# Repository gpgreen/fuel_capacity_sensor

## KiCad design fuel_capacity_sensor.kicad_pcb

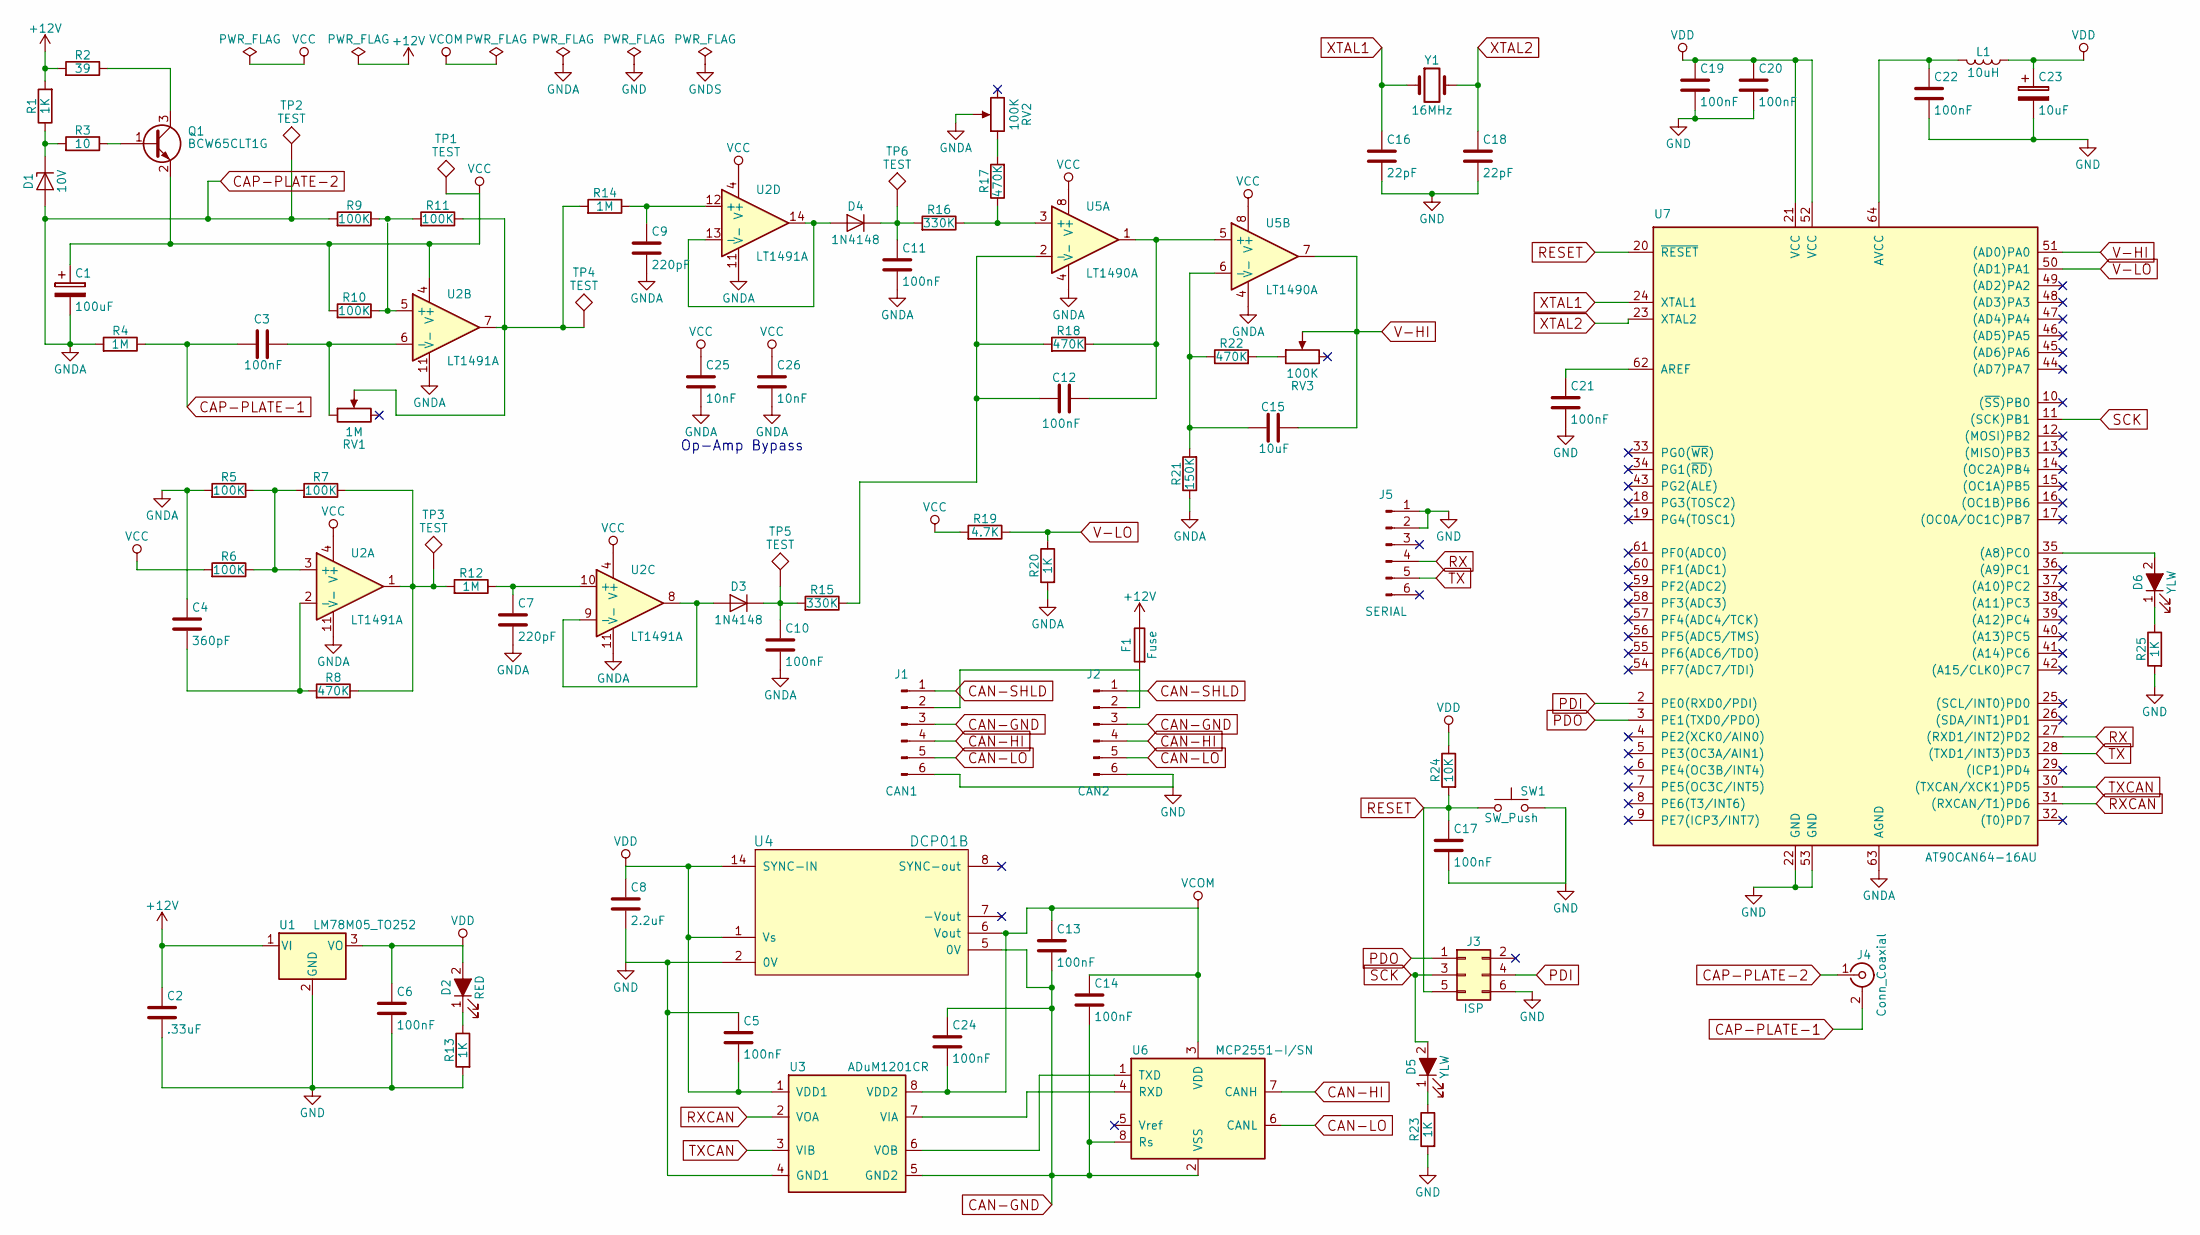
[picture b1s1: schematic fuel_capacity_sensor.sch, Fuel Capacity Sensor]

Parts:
C1: 100uF; C_0603
C2: .33uF; C_0603
C3, C5, C6, C10, C11, C12, C13, C14, C17, C19, C20, C21, C22, C24: 100nF; C_0603
C4: 360pF; C_0603
C7, C9: 220pF; C_0603
C8: 2.2uF; C_0603
C15: 10uF; C_0603
C16, C18: 22pF; C_0603
C23: 10uF; CP_Tantalum_Case-A_EIA-3216-18_Reflow
C25, C26: 10nF; C_0603
D1: 10V; D_SOD-123F
D2: RED; D_SOD-123F
D3, D4: 1N4148; D_SOD-123F
D5, D6: YLW; D_SOD-123F
F1: Fuse; Fuse_SMD1206_Reflow
J1: CAN1; JST_XH_B06B-XH-A_06x2.50mm_Straight
J2: CAN2; JST_XH_B06B-XH-A_06x2.50mm_Straight
J3: ISP
J4: Conn_Coaxial; bnc-ci
J5: SERIAL; Pin_Header_Straight_1x06_Pitch2.54mm
L1: 10uH; L_1206
Q1: BCW65CLT1G; SOT-23
R1, R13, R20, R23, R25: 1K; R_0603
R2: 39; R_0603
R3: 10; R_0603
R4, R12, R14: 1M; R_0603
R5, R6, R7, R9, R10, R11: 100K; R_0603
R8, R17, R18, R22: 470K; R_0603
R15, R16: 330K; R_0603
R19: 4.7K; R_0603
R21: 150K; R_0603
R24: 10K; R_0603
RV1: 1M; Potentiometer_Trimmer_Copal_CT-6EP
RV2, RV3: 100K; Potentiometer_Trimmer_Copal_CT-6EP
SW1: SW_Push; switch-kpt-1187B-SMD
TP1, TP2, TP3, TP4, TP5, TP6: TEST; Test_Point_Keystone_5015_Micro-Minature
U1: LM78M05_TO252; TO-252-2
U2: LT1491A; SOIC-16_3.9x9.9mm_Pitch1.27mm
U3: ADuM1201CR; SOIC-8_3.9x4.9mm_Pitch1.27mm
U4: DCP01B; DCP01B_SO_7_14
U5: LT1490A; SOIC-8_3.9x4.9mm_Pitch1.27mm
U6: MCP2551-I/SN; SOIC-8_3.9x4.9mm_Pitch1.27mm
U7: AT90CAN64-16AU; TQFP-64_10x10mm_Pitch0.5mm
Y1: 16MHz; Crystal_SMD_HC49-SD

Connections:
+12V: C2.1, F1.1, R1.2, R2.2, U1.1 (VI)
CAN-GND: C13.2, C14.2, C24.1, J1.3, J2.3, U3.5 (GND2), U4.5 (0V), U6.2 (VSS), U6.8 (Rs)
CAN-HI: J1.4, J2.4, U6.7 (CANH)
CAN-LO: J1.5, J2.5, U6.6 (CANL)
CAN-SHLD: J1.1, J2.1
CAP-PLATE-1: C3.1, J4.2 (Ext), R4.1
CAP-PLATE-2: C1.2, C4.1, C7.2, C9.2, C10.2, C11.2, C25.2, C26.2, D1.2 (A), J4.1 (In), R4.2, R5.2, R9.2, R20.2, R21.1, RV2.2, TP2.1, U2.11 (V-), U5.4 (V-), U7.63 (AGND)
GND: C2.2, C5.1, C6.2, C8.2, C16.2, C17.2, C18.2, C19.2, C20.2, C21.2, C22.2, C23.2, J1.6, J2.6, J3.6, J5.1, J5.2, R13.2, R23.2, R25.2, SW1.2, U1.2 (GND), U3.4 (GND1), U4.2 (0V), U7.22 (GND), U7.53 (GND)
unnamed: C3.2, RV1.1, U2.6 (-)
unnamed: C4.2, R8.2, U2.2 (-)
unnamed: C7.1, R12.1, U2.10 (+)
unnamed: C9.1, R14.1, U2.12 (+)
unnamed: C10.1, D3.1 (K), R15.2, TP5.1
unnamed: C11.1, D4.1 (K), R16.2, TP6.1
unnamed: C12.1, R15.1, R18.2, U5.2 (-)
unnamed: C12.2, R18.1, U5.1, U5.5 (+)
unnamed: C15.1, R21.2, R22.1, U5.6 (-)
unnamed: C21.1, U7.62 (AREF)
unnamed: C22.1, L1.2, U7.64 (AVCC)
unnamed: D1.1 (K), R1.1, R3.2
unnamed: D2.1 (K), R13.1
unnamed: D3.2 (A), U2.8, U2.9 (-)
unnamed: D4.2 (A), U2.13 (-), U2.14
unnamed: D5.1 (K), R23.1
unnamed: D6.1 (K), R25.1
unnamed: D6.2 (A), U7.35 ((A8)PC0)
unnamed: F1.2, J1.2, J2.2
unnamed: Q1.1 (B), R3.1
unnamed: Q1.3 (C), R2.1
unnamed: R5.1, R6.1, R7.2, U2.3 (+)
unnamed: R10.1, U2.5 (+)
unnamed: R11.1, R14.2, RV1.2, TP4.1, U2.7
unnamed: R9.1, R11.2
unnamed: R7.1, R8.1, R12.2, TP3.1, U2.1
unnamed: R16.1, R17.1, U5.3 (+)
unnamed: R17.2, RV2.1
unnamed: R22.2, RV3.1
unnamed: U3.6 (VOB), U6.1 (TXD)
unnamed: U3.7 (VIA), U6.4 (RXD)
PDI: J3.4, U7.2 (PE0(RXD0/PDI))
PDO: J3.1, U7.3 (PE1(TXD0/PDO))
RESET: C17.1, J3.5, R24.2, SW1.1, U7.20 (~RESET)
RX: J5.4, U7.27 ((RXD1/INT2)PD2)
RXCAN: U3.2 (VOA), U7.31 ((RXCAN/T1)PD6)
SCK: D5.2 (A), J3.3, U7.11 ((SCK)PB1)
TX: J5.5, U7.28 ((TXD1/INT3)PD3)
TXCAN: U3.3 (VIB), U7.30 ((TXCAN/XCK1)PD5)
V-HI: C15.2, RV3.2, U5.7, U7.51 ((AD0)PA0)
V-LO: R19.1, R20.1, U7.50 ((AD1)PA1)
VCC: C1.1, C25.1, C26.1, Q1.2 (E), R6.2, R10.2, R19.2, TP1.1, U2.4 (V+), U5.8 (V+)
VCOM: C13.1, C14.1, C24.2, U3.8 (VDD2), U4.6 (Vout), U6.3 (VDD)
VDD: C5.2, C6.1, C8.1, C19.1, C20.1, C23.1, D2.2 (A), L1.1, R24.1, U1.3 (VO), U3.1 (VDD1), U4.1 (Vs), U4.14 (SYNC-IN), U7.21 (VCC), U7.52 (VCC)
XTAL1: C16.1, U7.24 (XTAL1), Y1.1
XTAL2: C18.1, U7.23 (XTAL2), Y1.2

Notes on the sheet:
Op-Amp Bypass

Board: 2 copper layers, 83 parts (0 on the bottom side), 54 nets, no tracks yet.

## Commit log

2018-08-12 Added at90can32 and associated hw
2018-08-19 Added at90can32 and footprints
2018-08-26 Updated schematic and footprints
2018-09-10 Many updates
2018-10-05 Fixed ISP header
2020-12-15 New version of kicad changes
